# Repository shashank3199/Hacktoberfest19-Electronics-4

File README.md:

# Electronics-4

## Introduction
This repository contains the board design for Autonomous Bot Controller Shield for Arduino Mega 2560.

## Layout

### Board File -

### Schematic File -

## Files in the Repository
The files in the repository are :

#### AutonomousBot_Shield.brd
This is the Board file and contains the Blueprint of the Shield Layout (Prototype).

#### AutonomousBot_Shield.sch
This is the Schematic file and contains the actual circuitary behind the Shield.

#### README.md
The Description file containing details about the repository. The file that you looking at right now.

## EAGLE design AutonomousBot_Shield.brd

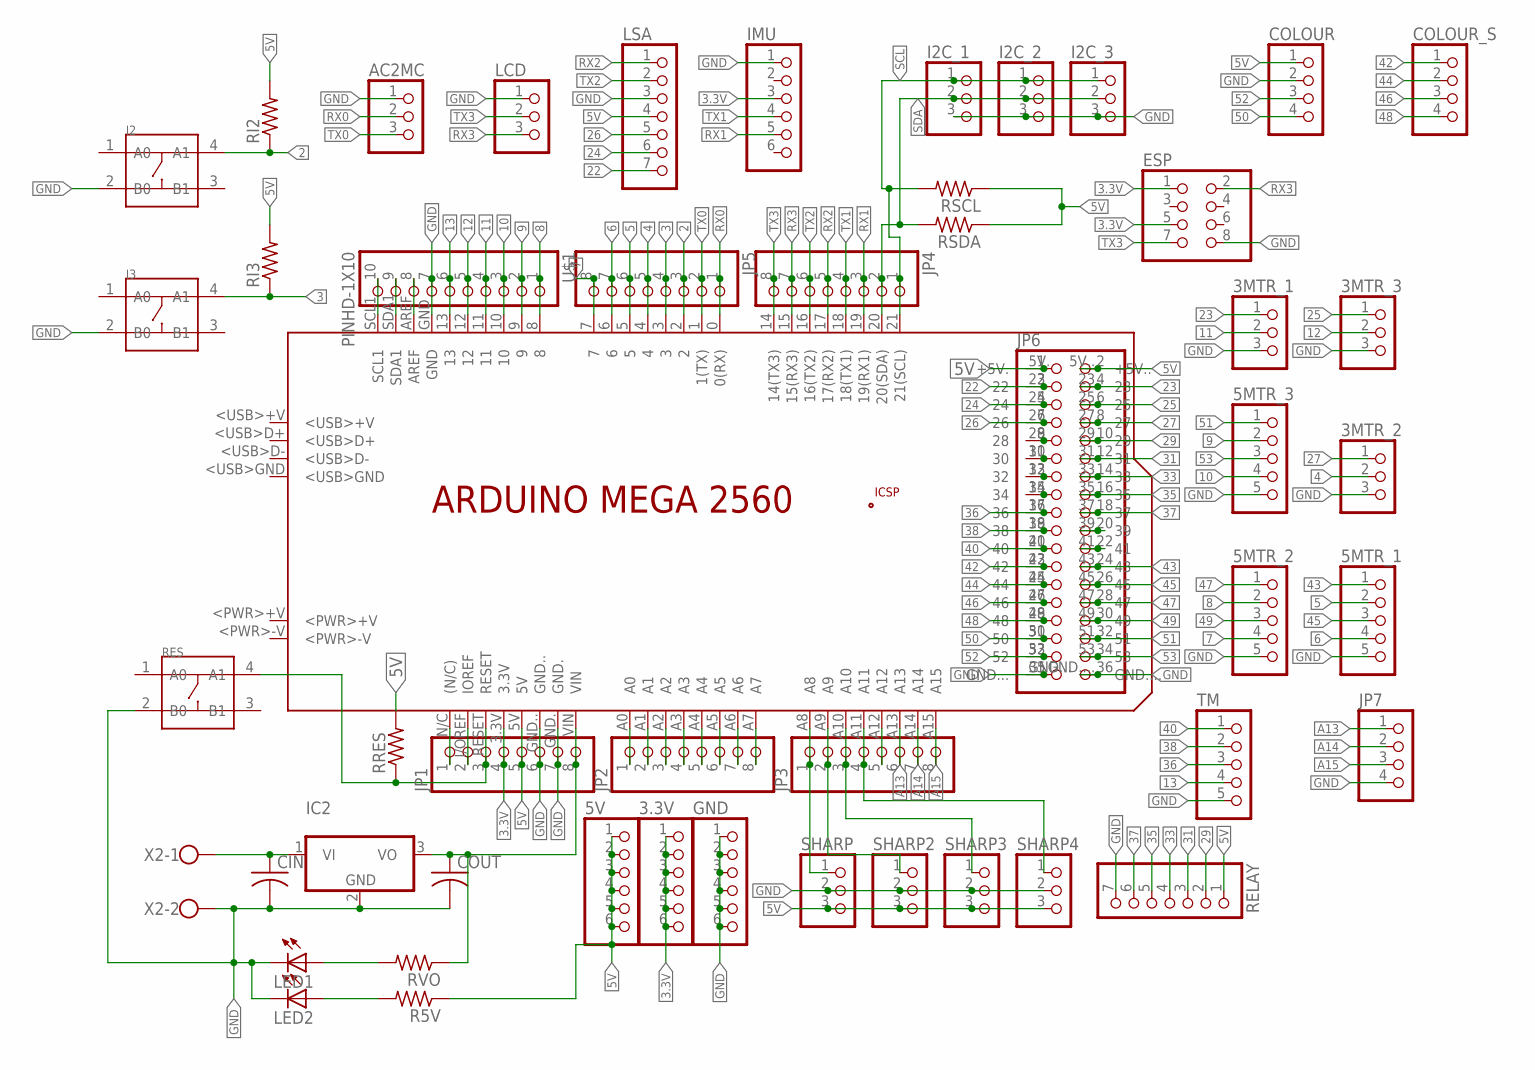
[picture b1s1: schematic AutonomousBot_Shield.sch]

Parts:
3.3V, 5V: PINHD-1X6; 1X06
3MTR_1, 3MTR_2, 3MTR_3: PINHD-1X3; 1X03
5MTR_1, 5MTR_2, 5MTR_3: PINHD-1X5; 1X05
AC2MC: PINHD-1X3; 1X03
CIN: C-US025-024X044; C025-024X044
COLOUR: PINHD-1X4; 1X04
COLOUR_S: PINHD-1X4; 1X04
COUT: C-US025-024X044; C025-024X044
ESP: PINHD-2X4; 2X04
GND: PINHD-1X6; 1X06
I2, I3: DIP-SWITCH-TACTILE-SPST-NO/TS-1109(4P-D6.0MM)'TS-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; SW4-6.0X6.0X5.0MM
I2C_1, I2C_2, I2C_3: PINHD-1X3; 1X03
IC2: 7812TV; TO220V
IMU: PINHD-1X6; 1X06
JP1, JP2, JP3, JP4, JP5: PINHD-1X8BIG; 1X08-BIG
JP6: PINHD-2X18; 2X18
JP7: PINHD-1X4; 1X04
LCD: PINHD-1X3; 1X03
LED1, LED2: LED5MM
LSA: PINHD-1X7; 1X07
PCB1: ARDUINO_MEGA2560
R5V: R-US_0207/7; 0207/7
RELAY: PINHD-1X7; 1X07
RES: DIP-SWITCH-TACTILE-SPST-NO/TS-1109(4P-D6.0MM)'TS-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; SW4-6.0X6.0X5.0MM
RI2, RI3: R-US_0207/7; 0207/7
RRES: R-US_0207/7; 0207/7
RSCL: R-US_0207/7; 0207/7
RSDA: R-US_0207/7; 0207/7
RVO: R-US_0207/7; 0207/7
SHARP, SHARP2, SHARP3, SHARP4: PINHD-1X3; 1X03
TM: PINHD-1X5; 1X05
U$1: PINHD-1X10; 1X10-BIG
X2: W237-102

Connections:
2: I2.4 (A1), JP5.3, PCB1.2, RI2.1
3: I3.4 (A1), JP5.4, PCB1.3, RI3.1
3.3V: 3.3V.1, 3.3V.2, 3.3V.3, 3.3V.4, 3.3V.5, 3.3V.6, ESP.1, ESP.5, IMU.3, JP1.4, PCB1.3.3V
4: 3MTR_2.2, JP5.5, PCB1.4
5: 5MTR_1.2, JP5.6, PCB1.5
5V: 5V.1, 5V.2, 5V.3, 5V.4, 5V.5, 5V.6, COLOUR.1, JP1.5, JP6.1, JP6.2, LSA.4, PCB1.5V, PCB1.5V. (+5V.), PCB1.5V.. (+5V..), R5V.1, RELAY.1, RI2.2, RI3.2, RRES.2, RSCL.1, RSDA.1, SHARP.3, SHARP2.3, SHARP3.3, SHARP4.3
6: 5MTR_1.4, JP5.7, PCB1.6
7: 5MTR_2.4, JP5.8, PCB1.7
8: 5MTR_2.2, PCB1.8, U$1.1
9: 5MTR_3.2, PCB1.9, U$1.2
10: 5MTR_3.4, PCB1.10, U$1.3
11: 3MTR_1.2, PCB1.11, U$1.4
12: 3MTR_3.2, PCB1.12, U$1.5
13: PCB1.13, TM.4, U$1.6
22: JP6.3, LSA.7, PCB1.22
23: 3MTR_1.1, JP6.4, PCB1.23
24: JP6.5, LSA.6, PCB1.24
25: 3MTR_3.1, JP6.6, PCB1.25
26: JP6.7, LSA.5, PCB1.26
27: 3MTR_2.1, JP6.8, PCB1.27
29: JP6.10, PCB1.29, RELAY.2
31: JP6.12, PCB1.31, RELAY.3
33: JP6.14, PCB1.33, RELAY.4
35: JP6.16, PCB1.35, RELAY.5
36: JP6.17, PCB1.36, TM.3
37: JP6.18, PCB1.37, RELAY.6
38: JP6.19, PCB1.38, TM.2
40: JP6.21, PCB1.40, TM.1
42: COLOUR_S.1, JP6.23, PCB1.42
43: 5MTR_1.1, JP6.24, PCB1.43
44: COLOUR_S.2, JP6.25, PCB1.44
45: 5MTR_1.3, JP6.26, PCB1.45
46: COLOUR_S.3, JP6.27, PCB1.46
47: 5MTR_2.1, JP6.28, PCB1.47
48: COLOUR_S.4, JP6.29, PCB1.48
49: 5MTR_2.3, JP6.30, PCB1.49
50: COLOUR.4, JP6.31, PCB1.50
51: 5MTR_3.1, JP6.32, PCB1.51
52: COLOUR.3, JP6.33, PCB1.52
53: 5MTR_3.3, JP6.34, PCB1.53
A13: JP3.6, JP7.1, PCB1.A13
A14: JP3.7, JP7.2, PCB1.A14
A15: JP3.8, JP7.3, PCB1.A15
GND: 3MTR_1.3, 3MTR_2.3, 3MTR_3.3, 5MTR_1.5, 5MTR_2.5, 5MTR_3.5, AC2MC.1, CIN.2, COLOUR.2, COUT.2, ESP.8, GND.1, GND.2, GND.3, GND.4, GND.5, GND.6, I2.2 (B0), I2C_1.3, I2C_2.3, I2C_3.3, I3.2 (B0), IC2.2 (GND), IMU.1, JP1.6, JP1.7, JP6.35, JP6.36, JP7.4, LCD.1, LED1.K (C), LED2.K (C), LSA.3, PCB1.GND, PCB1.GND., PCB1.GND.., PCB1.GND..., PCB1.GND...., RELAY.7, RES.2 (B0), SHARP.2, SHARP2.2, SHARP3.2, SHARP4.2, TM.5, U$1.7, X2.2
unnamed: CIN.1, IC2.1 (VI), X2.1
unnamed: COUT.1, IC2.3 (VO), JP1.8, PCB1.VIN, RVO.1
unnamed: LED2.A, R5V.2
unnamed: LED1.A, RVO.2
unnamed: JP1.3, PCB1.RESET, RES.4 (A1), RRES.1
unnamed: JP1.2, PCB1.I/OREF (IOREF)
unnamed: JP1.1, PCB1.N/C ((N/C))
unnamed: JP6.9, PCB1.28
unnamed: JP2.1, PCB1.A0
unnamed: JP2.2, PCB1.A1
unnamed: JP2.3, PCB1.A2
unnamed: JP2.4, PCB1.A3
unnamed: JP2.5, PCB1.A4
unnamed: JP6.20, PCB1.39
unnamed: JP6.22, PCB1.41
unnamed: JP2.6, PCB1.A5
unnamed: JP2.7, PCB1.A6
unnamed: JP2.8, PCB1.A7
unnamed: JP3.1, PCB1.A8, SHARP.1
unnamed: JP3.2, PCB1.A9, SHARP2.1
unnamed: JP3.3, PCB1.A10, SHARP3.1
unnamed: JP3.4, PCB1.A11, SHARP4.1
unnamed: JP3.5, PCB1.A12
unnamed: PCB1.AREF, U$1.8
unnamed: PCB1.SDA1, U$1.9
unnamed: PCB1.SCL1, U$1.10
unnamed: JP6.15, PCB1.34
unnamed: JP6.13, PCB1.32
unnamed: JP6.11, PCB1.30
RX0: AC2MC.2, JP5.1, PCB1.0 (0(RX))
RX1: IMU.5, JP4.3, PCB1.19 (19(RX1))
RX2: JP4.5, LSA.1, PCB1.17 (17(RX2))
RX3: ESP.2, JP4.7, LCD.3, PCB1.15 (15(RX3))
SCL: I2C_1.1, I2C_2.1, I2C_3.1, JP4.1, PCB1.21 (21(SCL)), RSCL.2
SDA: I2C_1.2, I2C_2.2, I2C_3.2, JP4.2, PCB1.20 (20(SDA)), RSDA.2
TX0: AC2MC.3, JP5.2, PCB1.1 (1(TX))
TX1: IMU.4, JP4.4, PCB1.18 (18(TX1))
TX2: JP4.6, LSA.2, PCB1.16 (16(TX2))
TX3: ESP.7, JP4.8, LCD.2, PCB1.14 (14(TX3))

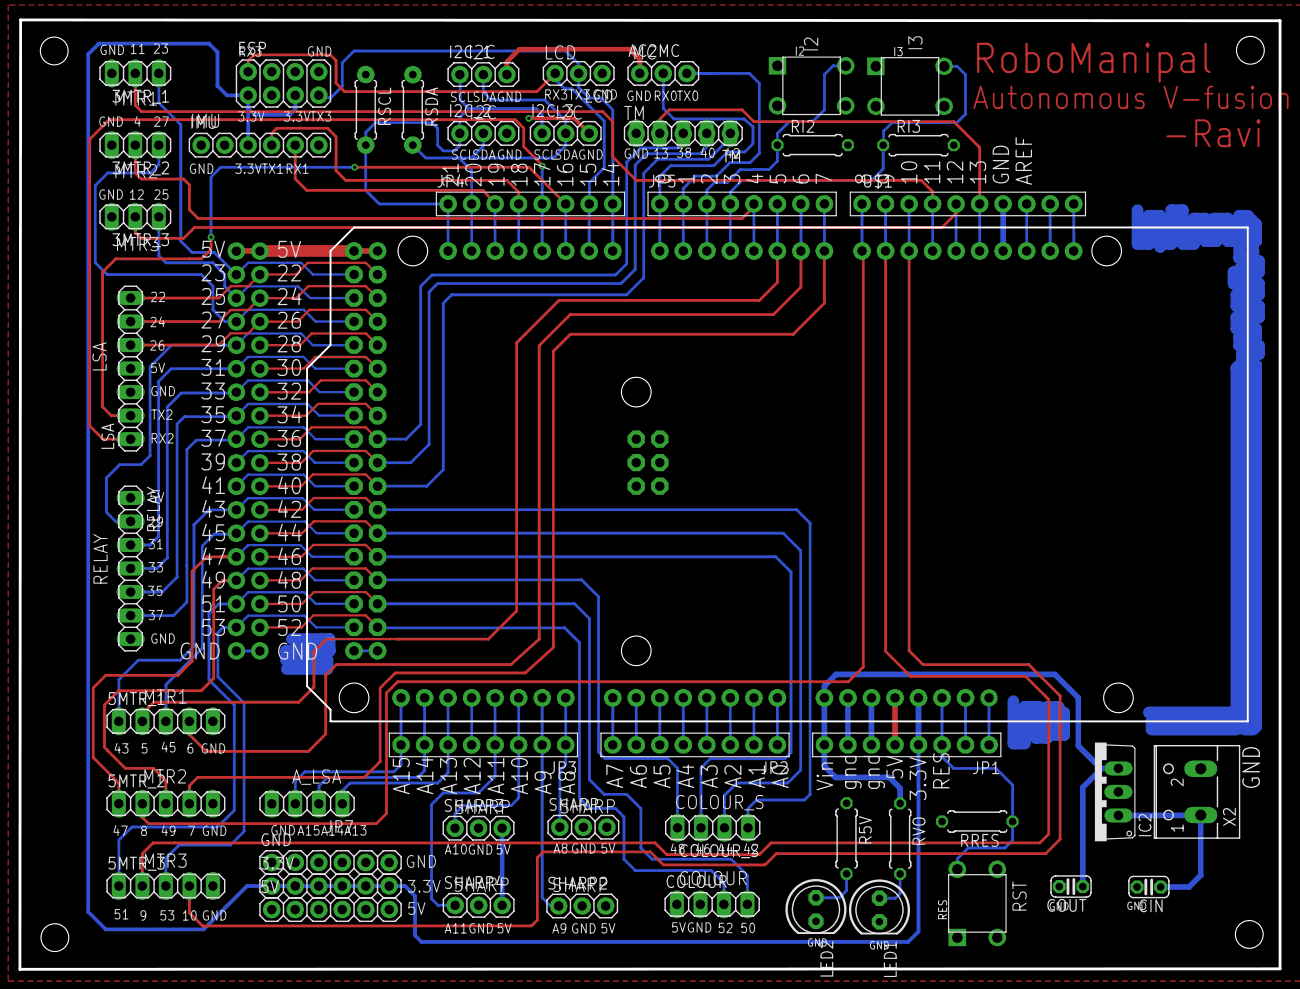
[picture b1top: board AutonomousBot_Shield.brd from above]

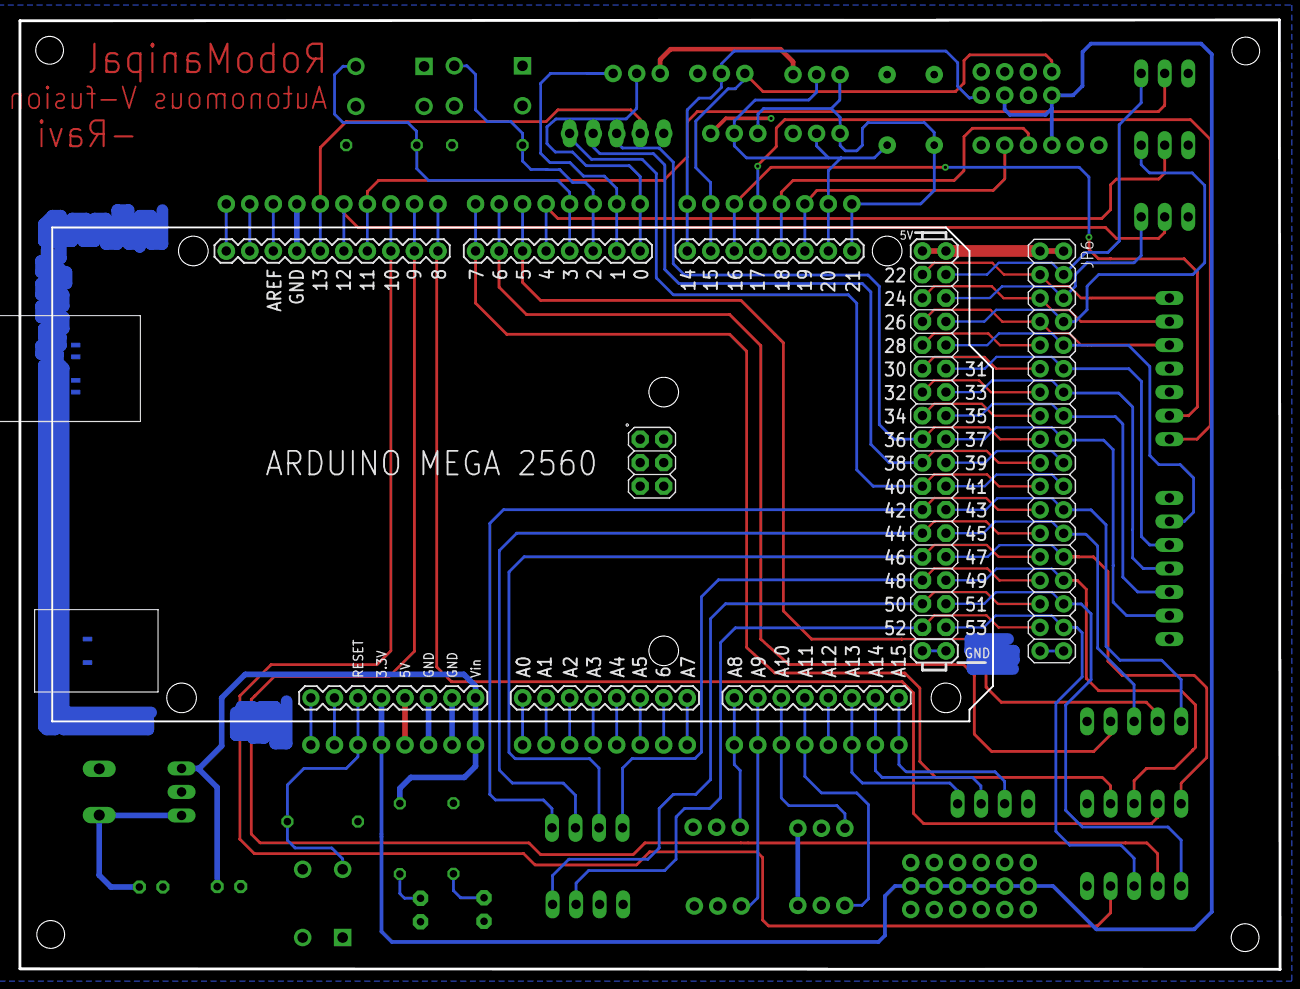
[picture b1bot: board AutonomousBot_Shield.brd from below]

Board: 2 copper layers, 136.1 x 102.5 mm, 50 parts (2 on the bottom side), 83 nets.

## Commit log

2019-10-02 comet4
2019-10-20 Added Documentation and Appropriate Naming
2019-10-20 Fixed Documentation
